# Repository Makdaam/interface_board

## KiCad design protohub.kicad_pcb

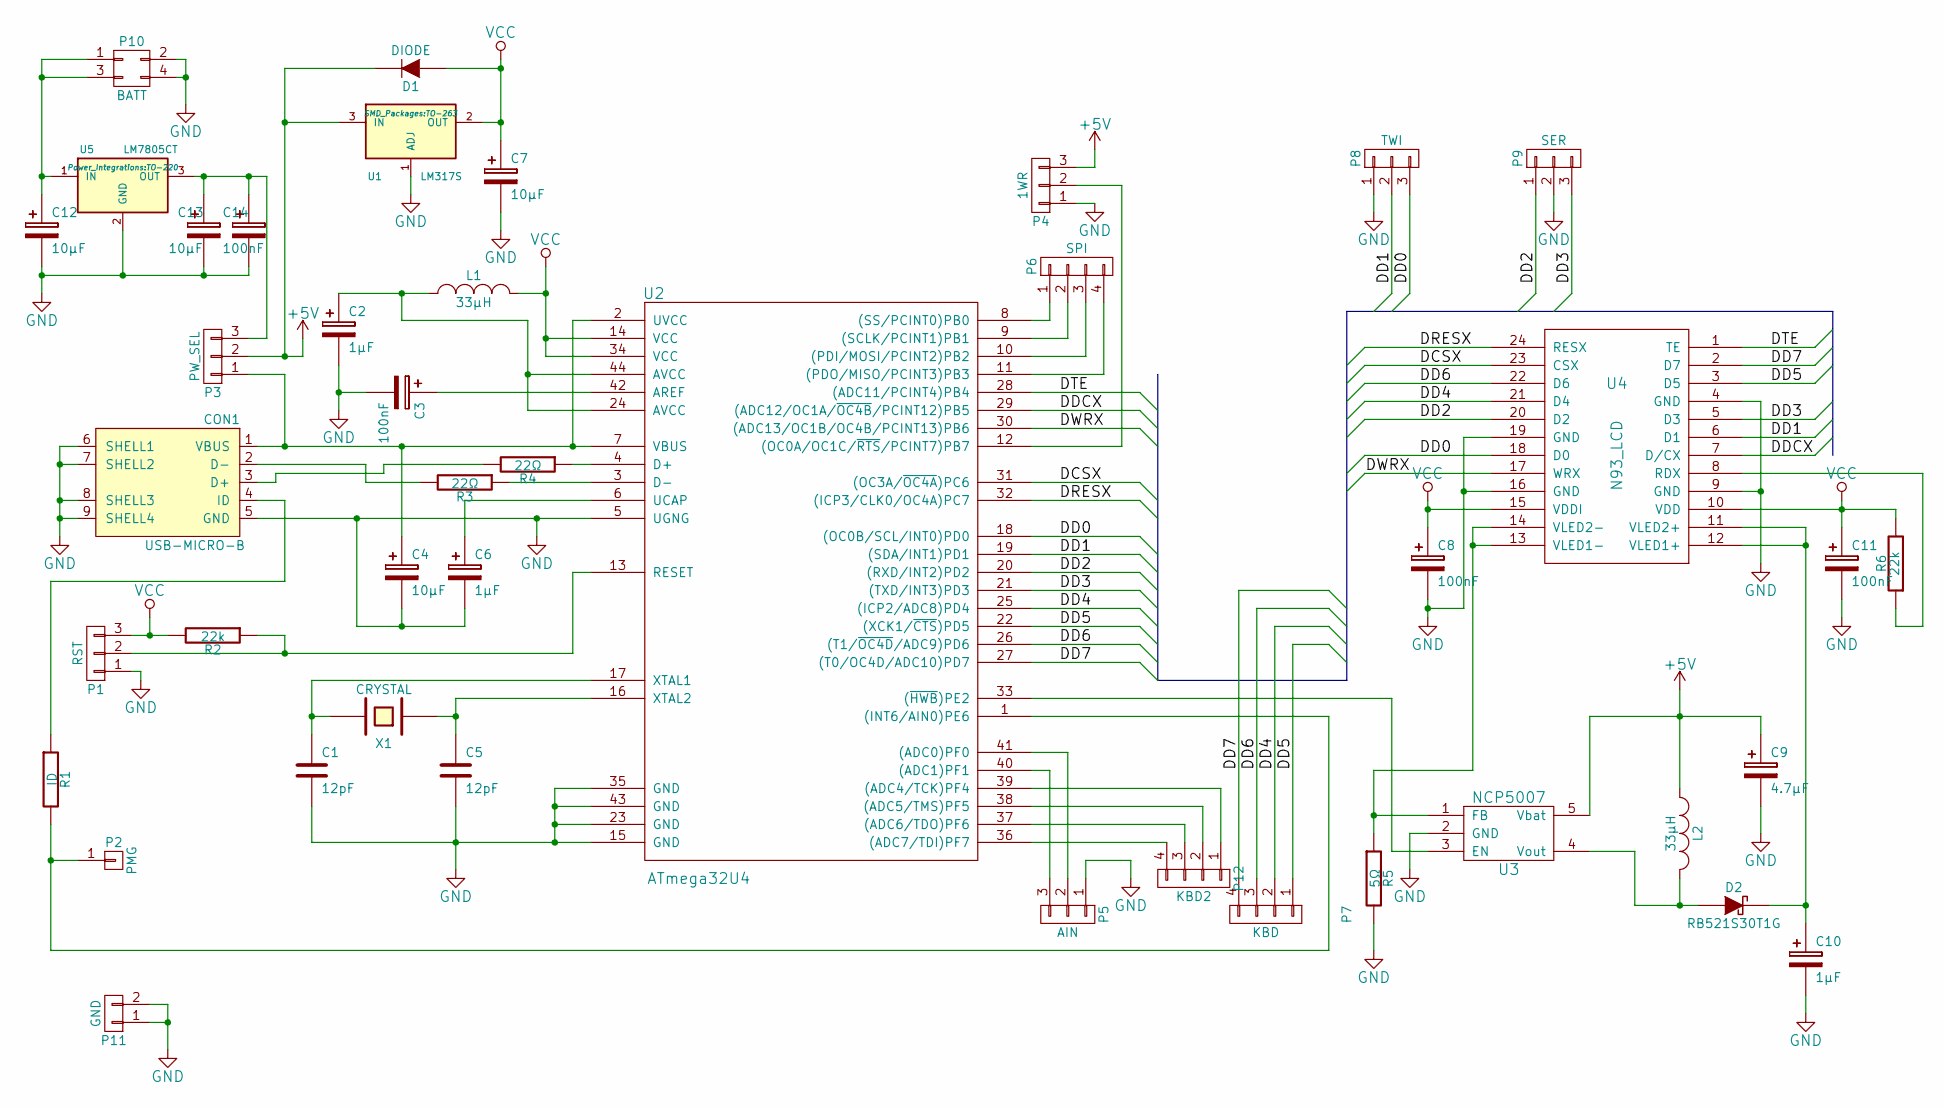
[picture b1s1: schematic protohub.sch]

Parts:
C1, C5: 12pF; C_0805_HandSoldering
C2, C6, C10: 1µF; c_elec_4x5.3
C3: 100nF; R_0805_HandSoldering
C4, C7, C12, C13: 10µF; c_elec_5x5.3
C8, C11, C14: 100nF; C_0805_HandSoldering
C9: 4.7µF; c_elec_4x5.3
CON1: USB-MICRO-B; USB_Micro-B
D1: DIODE; SMD-1812
D2: RB521S30T1G; SOD-523
L1, L2: 33µH; SMD-1812_l
P1: RST; Pin_Header_Straight_1x03
P2: PMG; Pin_Header_Straight_1x01
P3: PW_SEL; Pin_Header_Straight_1x03
P4: 1WR; Pin_Header_Straight_1x03
P5: AIN; Pin_Header_Straight_1x03
P6: SPI; Pin_Header_Straight_1x04
P7: KBD; Pin_Header_Straight_1x04
P8: TWI; Pin_Header_Straight_1x03
P9: SER; Pin_Header_Straight_1x03
P10: BATT; Pin_Header_Straight_2x02
P11: GND; Pin_Header_Straight_1x02
P12: KBD2; Pin_Header_Straight_1x04
R1: ID; R_0805_HandSoldering
R2, R6: 22k; R_0805_HandSoldering
R3, R4: 22Ω; R_0805_HandSoldering
R5: 5Ω; R_0805_HandSoldering
U1: LM317S; TO-263
U2: ATmega32U4; TQFP-44_10x10mm_Pitch0.8mm
U3: NCP5007; SOT-23-5
U4: N93_LCD; N93Disp
U5: LM7805CT; TO-220
X1: CRYSTAL; Crystal_HC49-U_Vertical

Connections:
+5V: C9.1, D1.2 (K), L2.1, P3.2, P4.3, U1.3 (IN), U3.5 (Vbat)
/DCSX: U2.31 ((OC3A/~OC4A~)PC6), U4.23 (CSX)
/DD0: P8.3, U2.18 ((OC0B/SCL/INT0)PD0), U4.18 (D0)
/DD1: P8.2, U2.19 ((SDA/INT1)PD1), U4.6 (D1)
/DD2: P9.1, U2.20 ((RXD/INT2)PD2), U4.20 (D2)
/DD3: P9.3, U2.21 ((TXD/INT3)PD3), U4.5 (D3)
/DD4: P7.2, U2.25 ((ICP2/ADC8)PD4), U4.21 (D4)
/DD5: P7.1, U2.22 ((XCK1/~CTS~)PD5), U4.3 (D5)
/DD6: P7.3, U2.26 ((T1/~OC4D~/ADC9)PD6), U4.22 (D6)
/DD7: P7.4, U2.27 ((T0/OC4D/ADC10)PD7), U4.2 (D7)
/DDCX: U2.29 ((ADC12/OC1A/~OC4B~/PCINT12)PB5), U4.7 (D/CX)
/DRESX: U2.32 ((ICP3/CLK0/OC4A)PC7), U4.24 (RESX)
/DTE: U2.28 ((ADC11/PCINT4)PB4), U4.1 (TE)
/DWRX: U2.30 ((ADC13/OC1B/OC4B/PCINT13)PB6), U4.17 (WRX)
GND: C1.2, C2.2, C3.2, C4.2, C5.2, C6.2, C7.2, C8.2, C9.2, C10.2, C11.2, C12.2, C13.2, C14.2, CON1.5 (GND), CON1.6 (SHELL1), CON1.7 (SHELL2), CON1.8 (SHELL3), CON1.9 (SHELL4), P1.1, P4.1, P5.1, P8.1, P9.2, P10.2, P10.4, P11.1, P11.2, R5.2, U1.1 (ADJ), U2.5 (UGNG), U2.15 (GND), U2.23 (GND), U2.35 (GND), U2.43 (GND), U3.2 (GND), U4.4 (GND), U4.9 (GND), U4.16 (GND), U4.19 (GND), U5.2 (GND)
unnamed: C1.1, U2.17 (XTAL1), X1.2
unnamed: C2.1, L1.1, U2.24 (AVCC), U2.44 (AVCC)
unnamed: C3.1, U2.42 (AREF)
unnamed: C4.1, CON1.1 (VBUS), P3.1, U2.2 (UVCC), U2.7 (VBUS)
unnamed: C5.1, U2.16 (XTAL2), X1.1
unnamed: C6.1, U2.6 (UCAP)
unnamed: C10.1, D2.2 (K), U4.11 (VLED2+), U4.12 (VLED1+)
unnamed: C12.1, P10.1, P10.3, U5.1 (IN)
unnamed: C13.1, C14.1, P3.3, U5.3 (OUT)
unnamed: CON1.2 (D-), R3.2
unnamed: CON1.3 (D+), R4.2
unnamed: CON1.4 (ID), R1.1
unnamed: D2.1 (A), L2.2, U3.4 (Vout)
unnamed: P1.2, R2.1, U2.13 (RESET)
unnamed: P2.1, R1.2, U2.1 ((INT6/AIN0)PE6)
unnamed: P4.2, U2.12 ((OC0A/OC1C/~RTS~/PCINT7)PB7)
unnamed: P5.2, U2.41 ((ADC0)PF0)
unnamed: P5.3, U2.40 ((ADC1)PF1)
unnamed: P6.1, U2.8 ((SS/PCINT0)PB0)
unnamed: P6.2, U2.9 ((SCLK/PCINT1)PB1)
unnamed: P6.3, U2.10 ((PDI/MOSI/PCINT2)PB2)
unnamed: P6.4, U2.11 ((PDO/MISO/PCINT3)PB3)
unnamed: P12.1, U2.39 ((ADC4/TCK)PF4)
unnamed: P12.2, U2.38 ((ADC5/TMS)PF5)
unnamed: P12.3, U2.37 ((ADC6/TDO)PF6)
unnamed: P12.4, U2.36 ((ADC7/TDI)PF7)
unnamed: R3.1, U2.3 (D-)
unnamed: R4.1, U2.4 (D+)
unnamed: R5.1, U3.1 (FB), U4.13 (VLED1-), U4.14 (VLED2-)
unnamed: R6.1, U4.8 (RDX)
unnamed: U2.33 ((~HWB~)PE2), U3.3 (EN)
VCC: C7.1, C8.1, C11.1, D1.1 (A), L1.2, P1.3, R2.2, R6.2, U1.2 (OUT), U2.14 (VCC), U2.34 (VCC), U4.10 (VDD), U4.15 (VDDI)

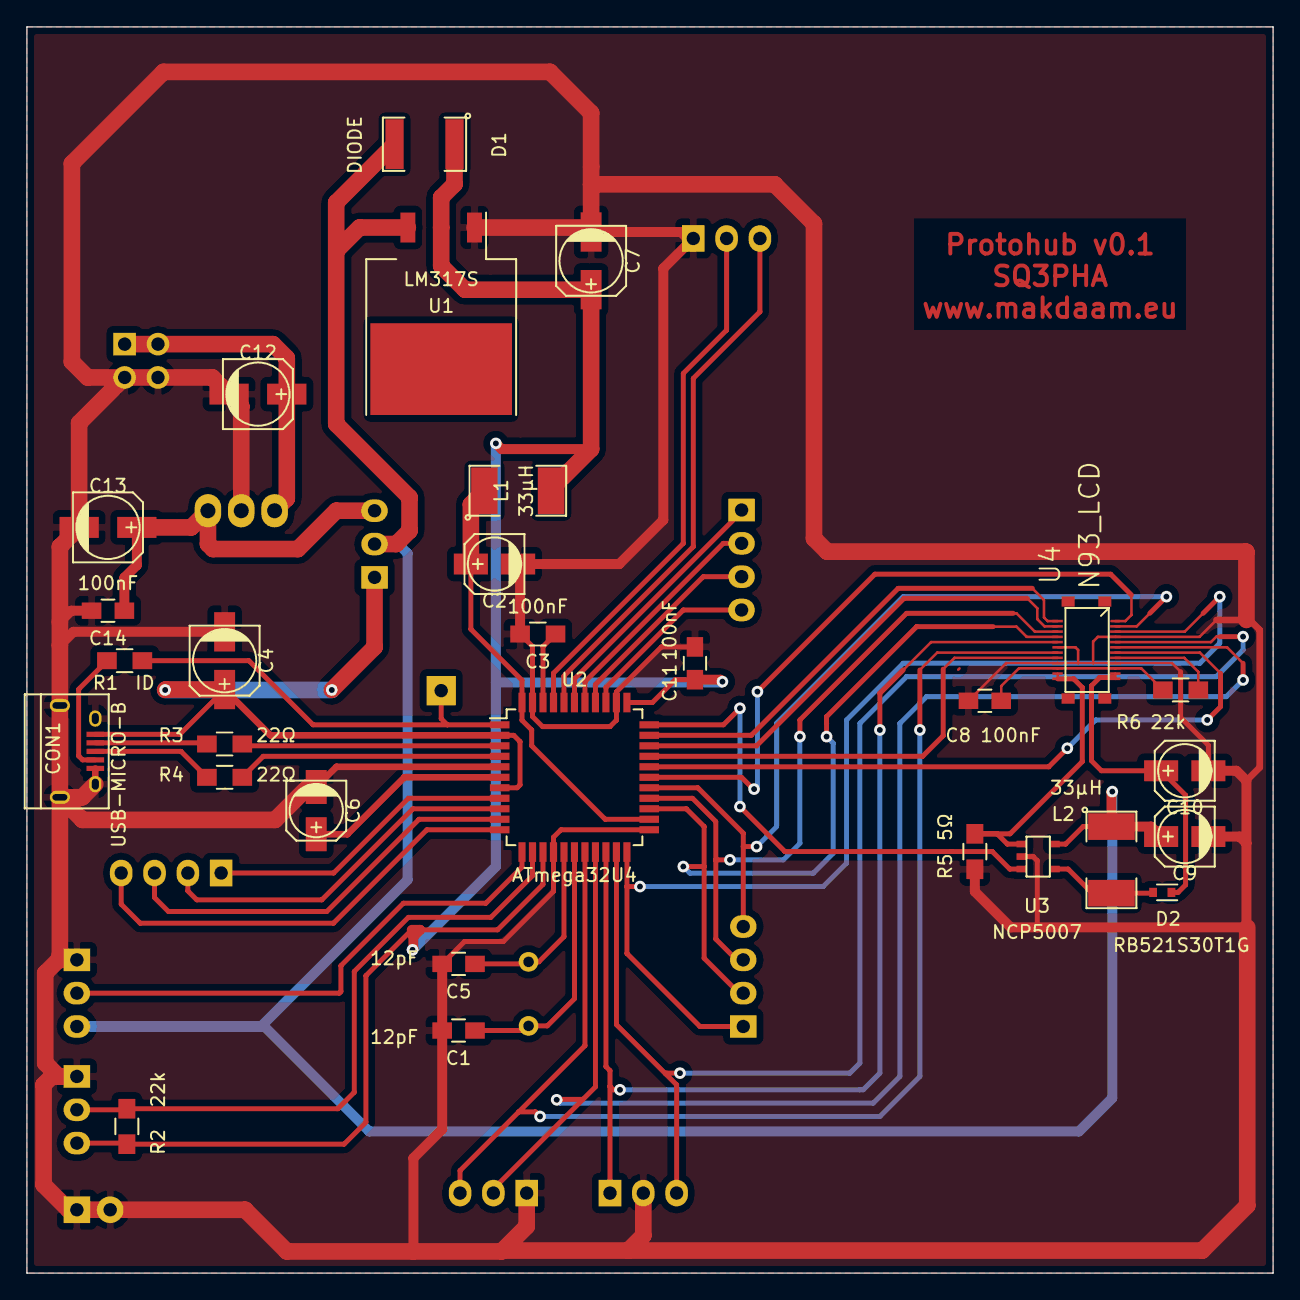
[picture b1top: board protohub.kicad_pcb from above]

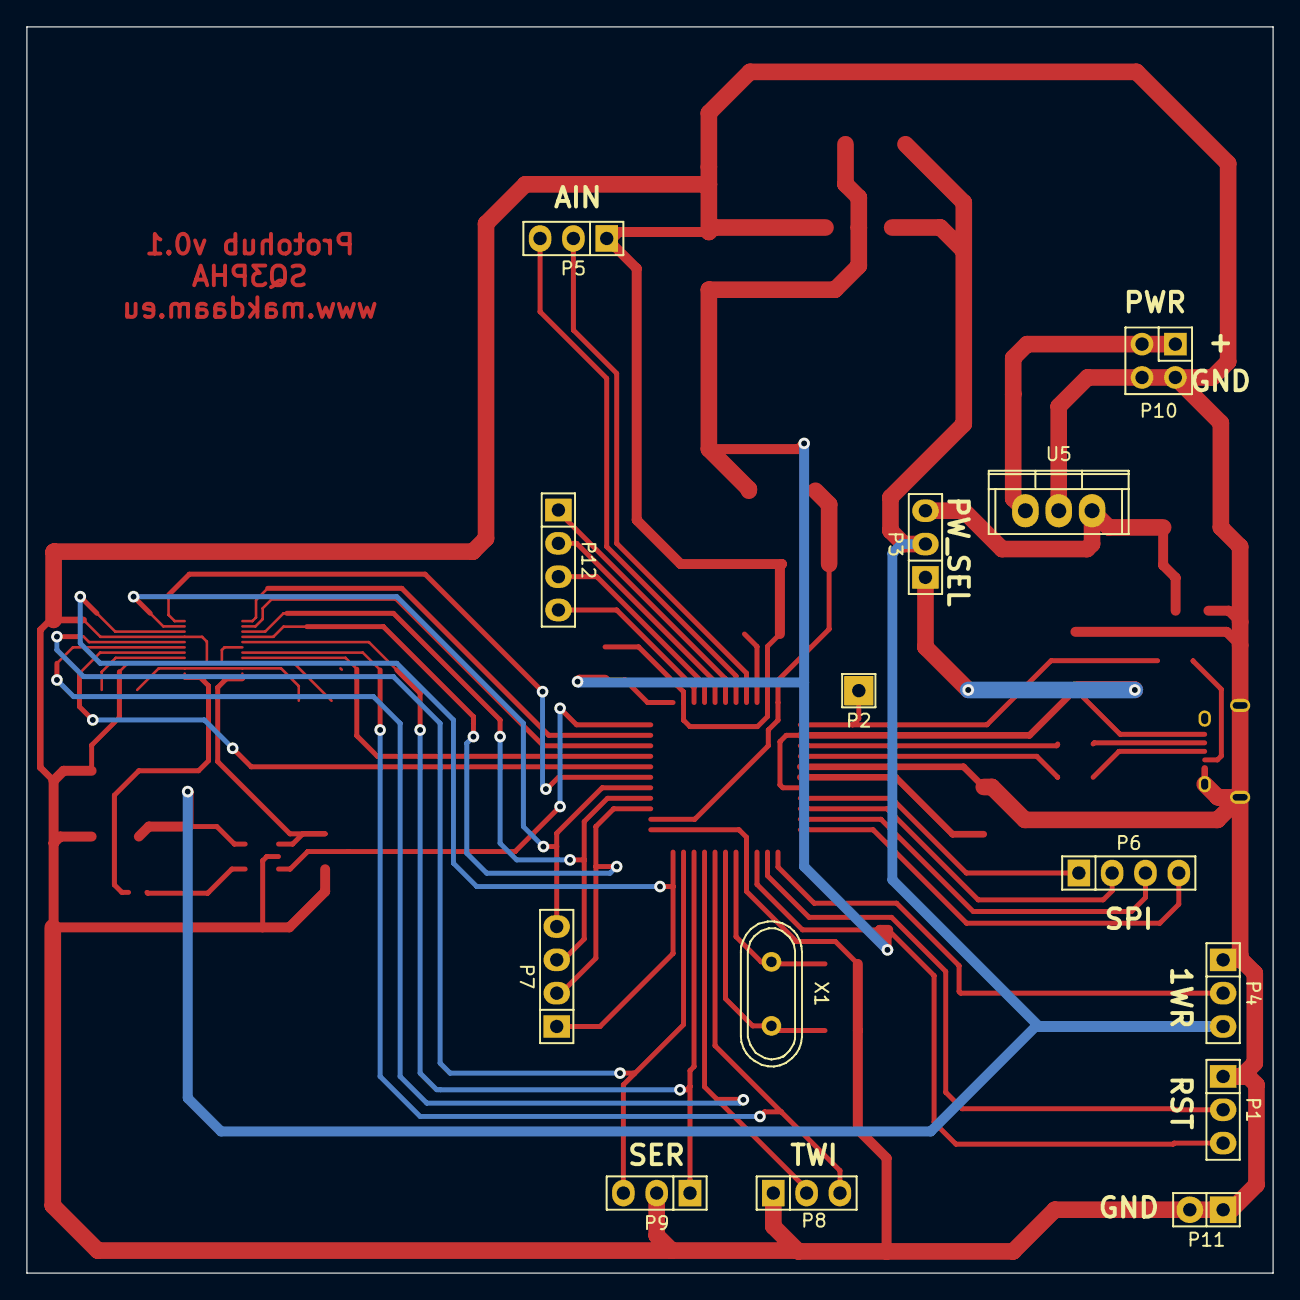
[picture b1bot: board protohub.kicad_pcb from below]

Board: 2 copper layers, 95.0 x 95.0 mm, 43 parts (14 on the bottom side), 47 nets.

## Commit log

2015-04-06 hardware prototype 0.1
2015-04-06 added License
